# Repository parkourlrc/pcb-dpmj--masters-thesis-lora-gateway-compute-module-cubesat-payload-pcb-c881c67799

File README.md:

# Hardware design of a LoRa Gateway and in-orbit computing payload for CubeSat.

This repository contains the hardware design files from my second Master's Thesis in Telecommunications Engineering at the Polytechnic University of Valencia, Spain, 2024. The payload consists of a CubeSat-PC/104 form factor motherboard that integrates LoRa gateway hardware and a Raspberry Pi Compute Module 5 for in-orbit computing tasks. 

This project is a continuation of my previous master's thesis: [Hardware design of a LoRa Gateway payload for CubeSat.](https://github.com/dpmj/masters-thesis-lora-gateway-cubesat-payload-pcb/)

Third-party desing elements included in this repository are subject to the copyright of their respective owners.

```bibtex
@phdthesis{dpmj-master-thesis-2025,
    author = {{Del Pino Mena}, Juan},
    title = {Development of a {CubeSat} payload for in-orbit computing and {LoRa} communications},
    school = {Universitat Politècnica de València},
    year = {2025},
    month = {9},
    address = {València, Spain},
    type = {Master's thesis},
    doi = {https://doi.org/10.5281/zenodo.16641815}
}
```

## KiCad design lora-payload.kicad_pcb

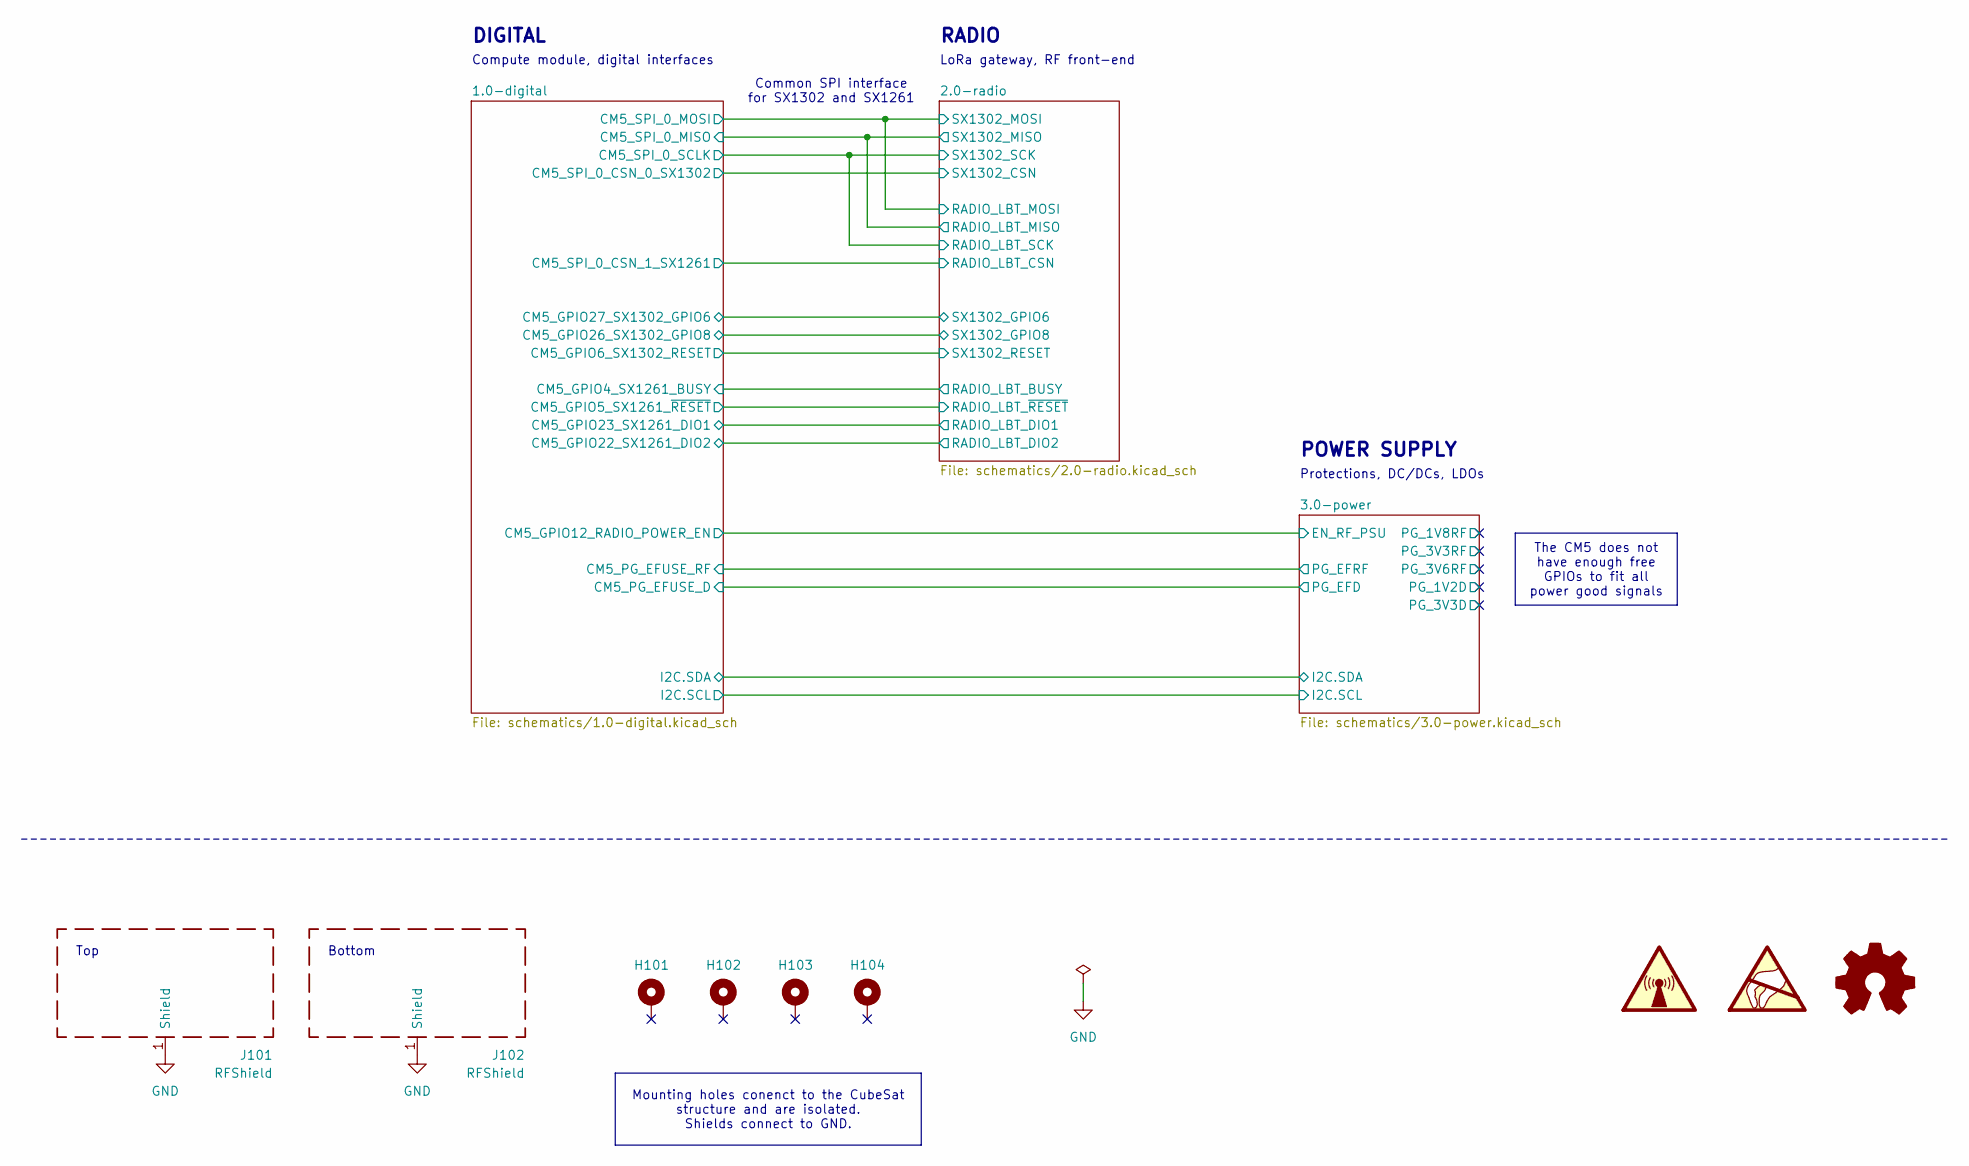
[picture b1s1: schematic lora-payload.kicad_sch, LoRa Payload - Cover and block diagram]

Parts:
H101, H102, H103, H104: MountingHole_Pad; MountingHole_3.2mm_M3_Pad
J101: RFShield; top_shield_payload
J102: RFShield; bottom_shield_payload

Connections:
GND: J101.1 (Shield), J102.1 (Shield); also elsewhere on the board

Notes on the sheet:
Protections, DC/DCs, LDOs
POWER SUPPLY
Common SPI interface for SX1302 and SX1261
Compute module, digital interfaces
LoRa gateway, RF front-end
RADIO
Top
DIGITAL
Bottom
The CM5 does not have enough free GPIOs to fit all power good signals
Mounting holes conenct to the CubeSat structure and are isolated. Shields connect to GND.

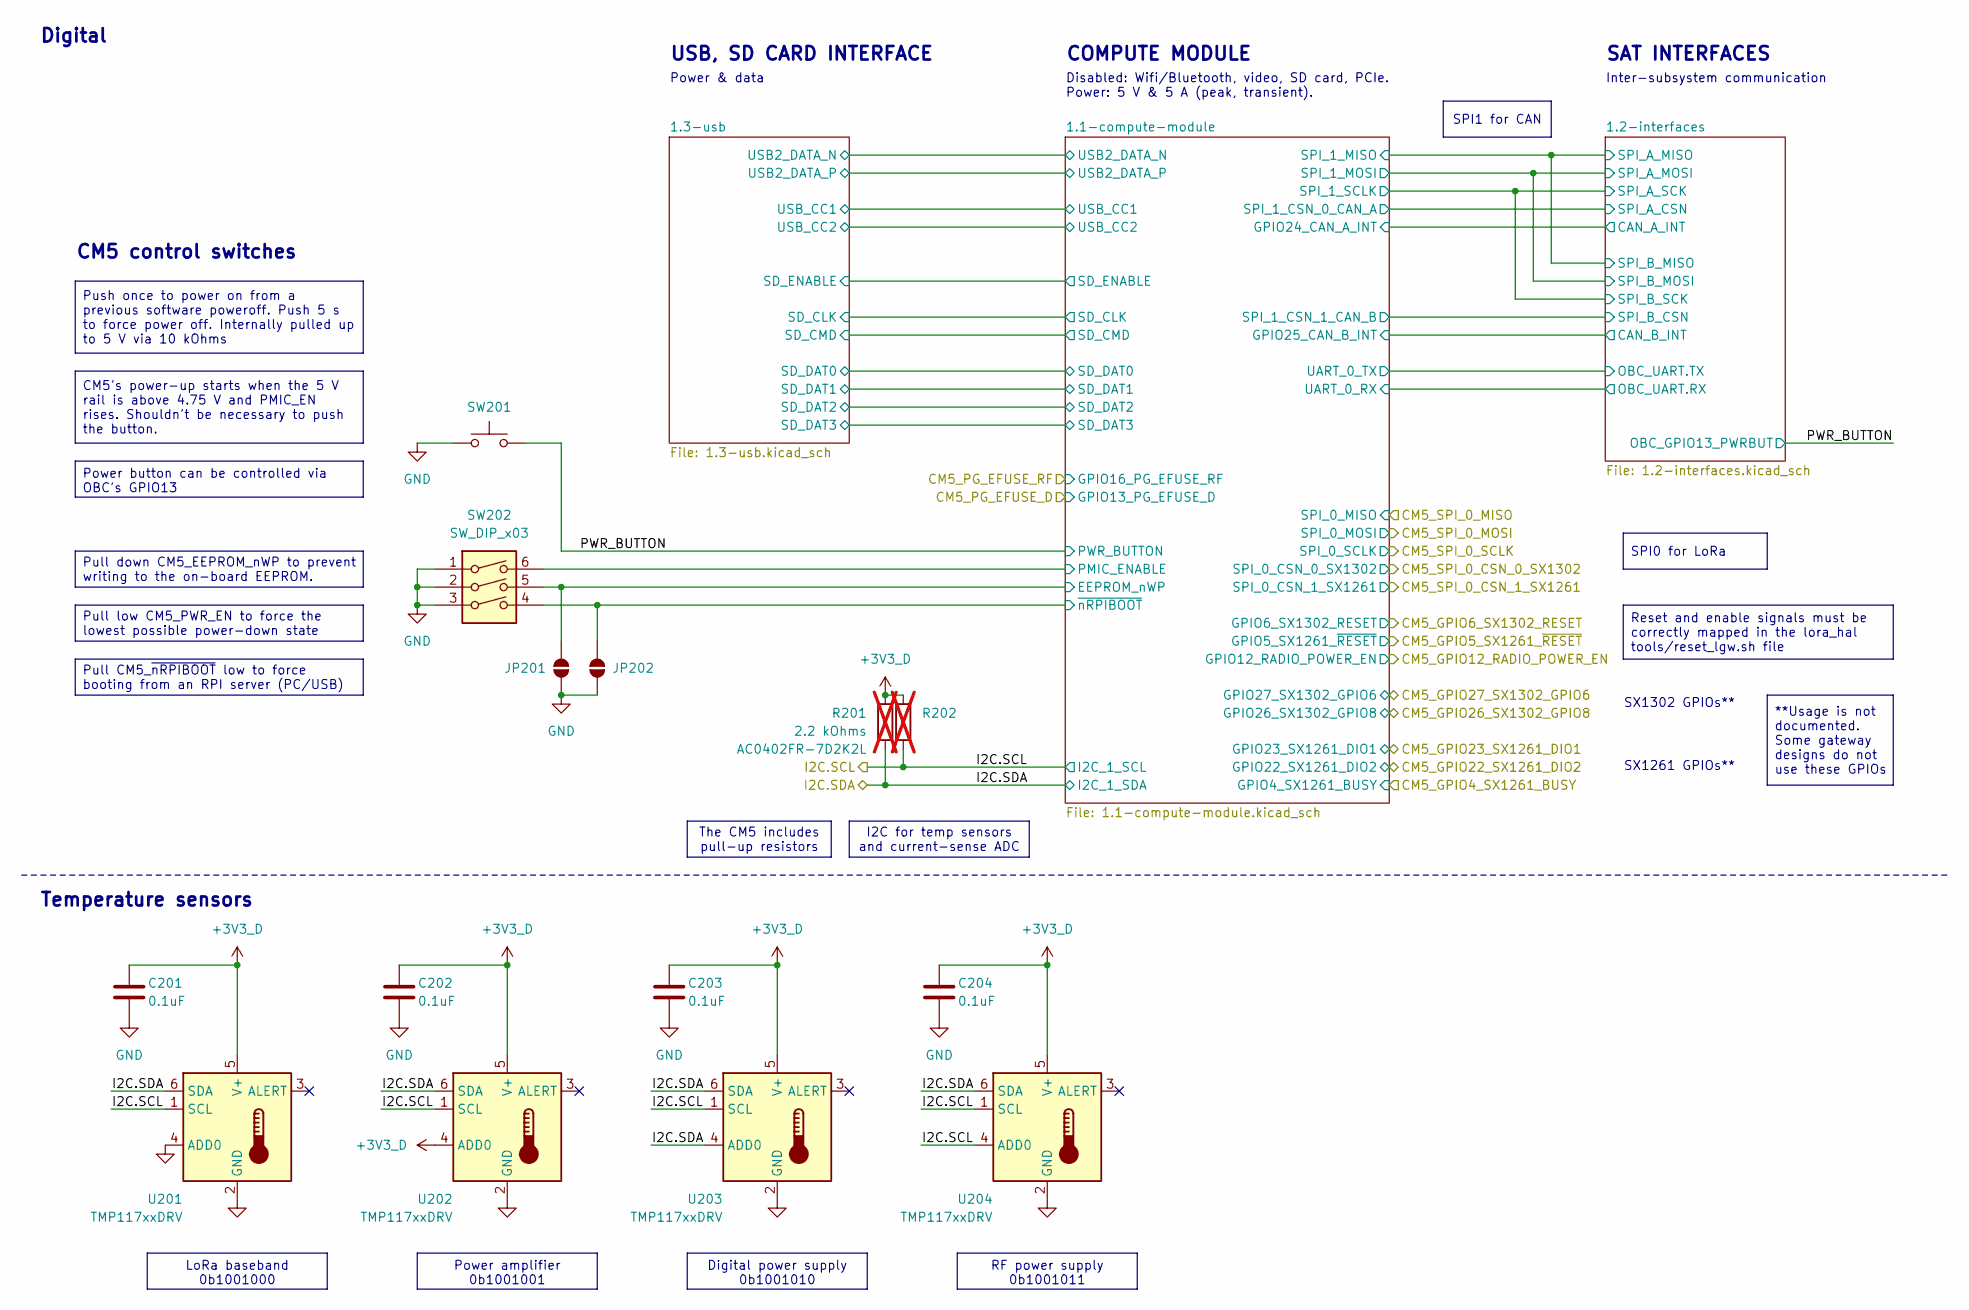
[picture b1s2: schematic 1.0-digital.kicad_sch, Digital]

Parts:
C201, C202, C203, C204: 0.1uF; C_0402_1005Metric; PartNumber GRM155R71C104KA88J
JP201, JP202: SolderJumper_2_Open; SolderJumper-2_P1.3mm_Open_RoundedPad1.0x1.5mm
R201: 2.2 kOhms; R_0402_1005Metric; PartNumber AC0402FR-7D2K2L; not fitted
R202: 2.2 kOhm; R_0402_1005Metric; PartNumber AC0402FR-7D2K2L; not fitted
SW201: SW_Push; SW_Push_1P1T_NO_Vertical_Wuerth_434133025816
SW202: SW_DIP_x03; SW_DIP_SPSTx03_Slide_KingTek_DSHP03TJ_W5.25mm_P1.27mm_JPin
U201, U202, U203, U204: TMP117xxDRV; WSON-6-1EP_2x2mm_P0.65mm_EP1x1.6mm

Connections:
+3V3_D: C201.2, C202.2, C203.2, C204.2, R201.1, R202.1, U201.5 (V+), U202.4 (ADD0), U202.5 (V+), U203.5 (V+), U204.5 (V+); also elsewhere on the board
/1.0-digital/1.1-compute-module/EEPROM_nWP: JP201.2 (B), SW202.5; also elsewhere on the board
/1.0-digital/1.1-compute-module/PMIC_ENABLE: SW202.6; also elsewhere on the board
/1.0-digital/1.1-compute-module/~nRPIBOOT: JP202.2 (B), SW202.4; also elsewhere on the board
/1.0-digital/I2C.SCL: R202.2, U201.1 (SCL), U202.1 (SCL), U203.1 (SCL), U204.1 (SCL), U204.4 (ADD0); also elsewhere on the board
/1.0-digital/I2C.SDA: R201.2, U201.6 (SDA), U202.6 (SDA), U203.4 (ADD0), U203.6 (SDA), U204.6 (SDA); also elsewhere on the board
/1.0-digital/PWR_BUTTON: SW201.2; also elsewhere on the board
GND: C201.1, C202.1, C203.1, C204.1, JP201.1 (A), JP202.1 (A), SW201.1, SW202.1, SW202.2, SW202.3, U201.2 (GND), U201.4 (ADD0), U202.2 (GND), U203.2 (GND), U204.2 (GND); also elsewhere on the board

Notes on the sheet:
SX1261 GPIOs**
SAT INTERFACES
COMPUTE MODULE
Inter-subsystem communication
Disabled: Wifi/Bluetooth, video, SD card, PCIe. Power: 5 V & 5 A (peak, transient).
Temperature sensors
Digital
USB, SD CARD INTERFACE
SX1302 GPIOs**
Power & data
CM5 control switches
SPI0 for LoRa
The CM5 includes pull-up resistors
Pull CM5_~{nRPIBOOT} low to force booting from an RPI server (PC/USB)
Pull low CM5_PWR_EN to force the lowest possible power-down state
LoRa baseband 0b1001000
SPI1 for CAN
**Usage is not documented. Some gateway designs do not use these GPIOs
CM5's power-up starts when the 5 V rail is above 4.75 V and PMIC_EN rises. Shouldn't be necessary to push the button.
RF power supply 0b1001011
Digital power supply 0b1001010
Power button can be controlled via OBC's GPIO13
Push once to power on from a previous software poweroff. Push 5 s to force power off. Internally pulled up to 5 V via 10 kOhms
Power amplifier 0b1001001
Reset and enable signals must be correctly mapped in the lora_hal tools/reset_lgw.sh file
I2C for temp sensors and current-sense ADC
Pull down CM5_EEPROM_nWP to prevent writing to the on-board EEPROM.

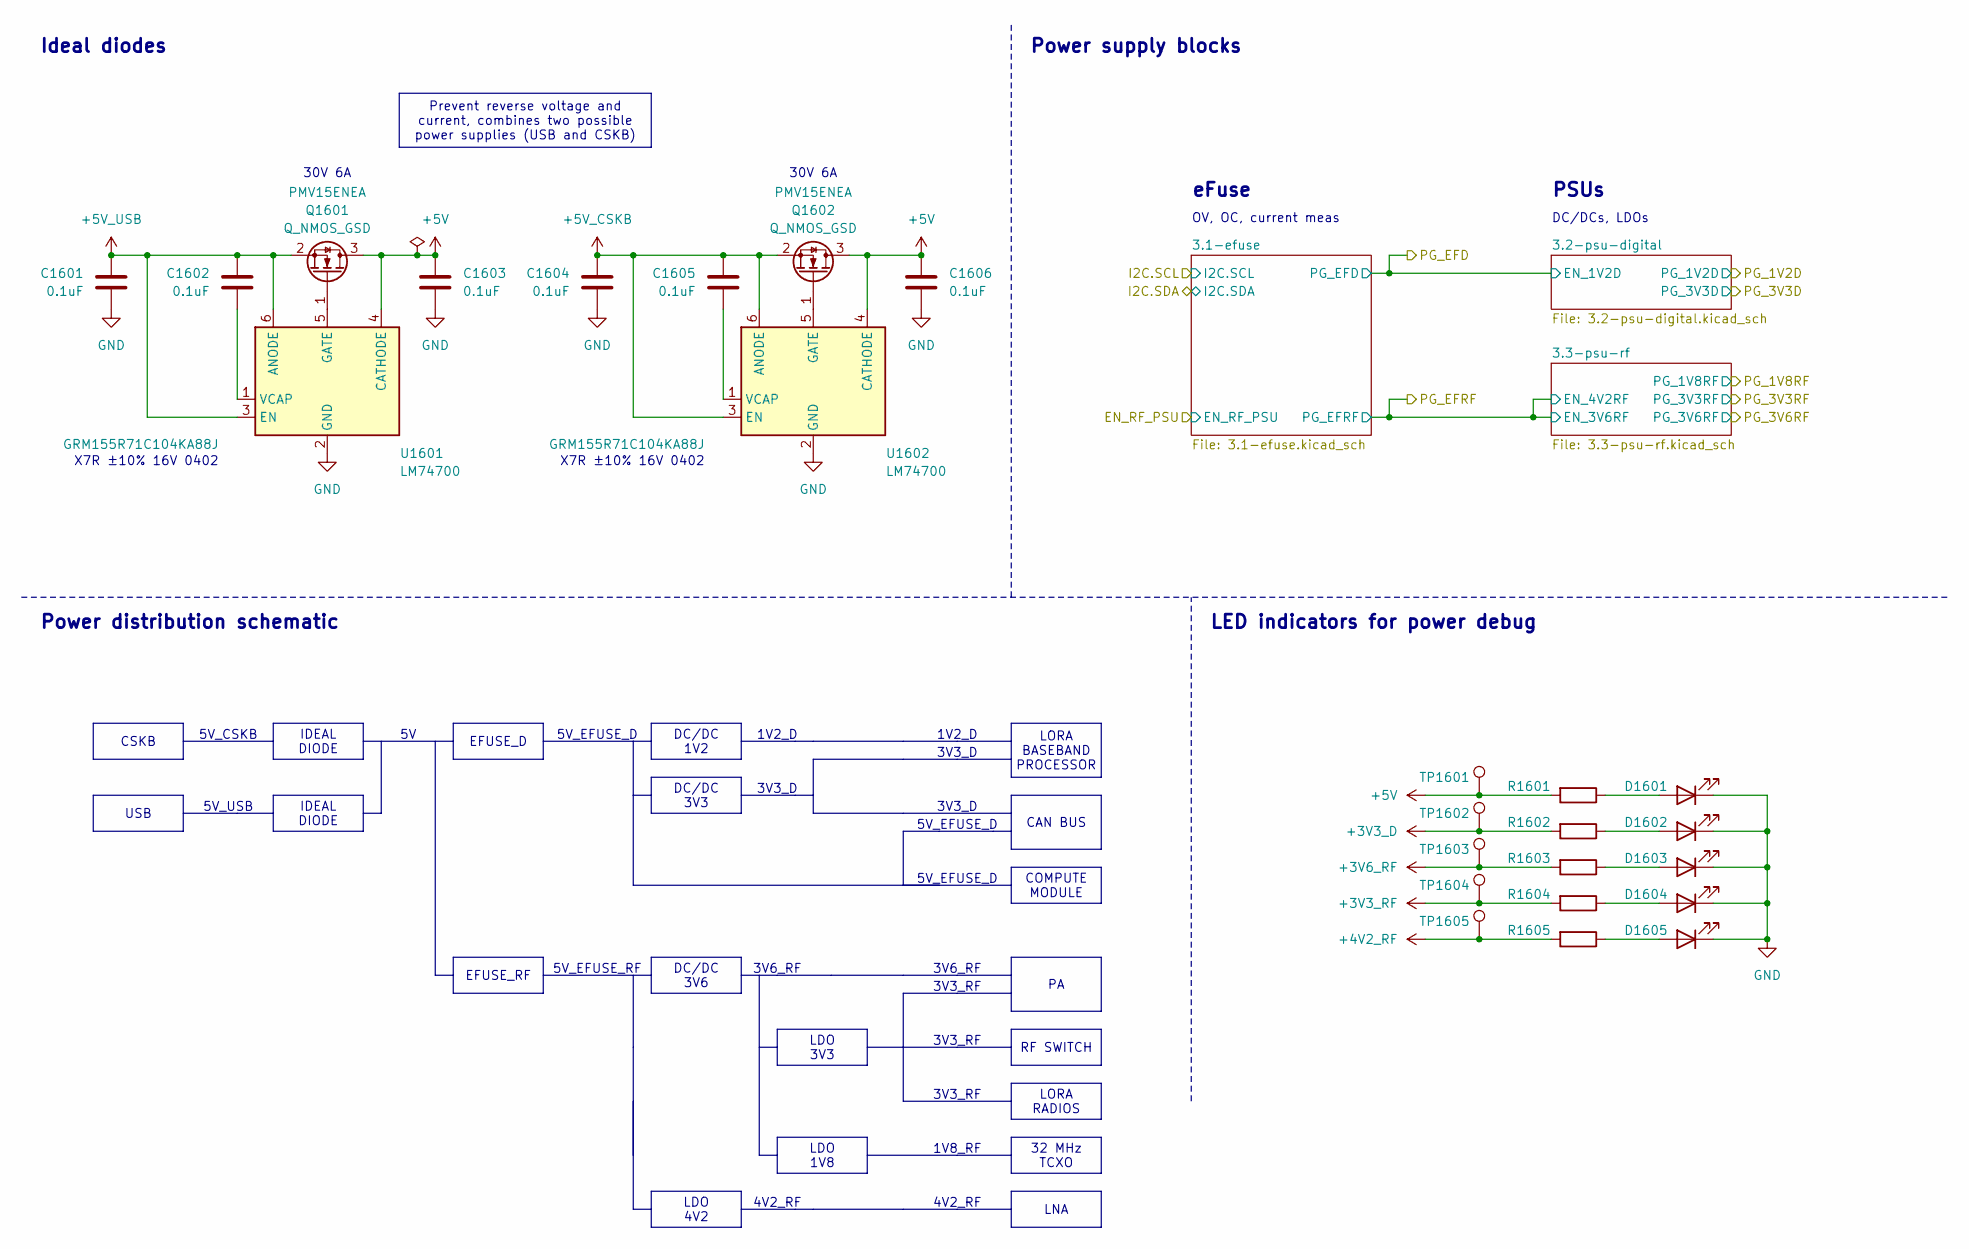
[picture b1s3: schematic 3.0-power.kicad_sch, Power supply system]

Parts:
C1601, C1602, C1603, C1604, C1605, C1606: 0.1uF; C_0402_1005Metric; PartNumber GRM155R71C104KA88J
D1601, D1602, D1603, D1604, D1605: Green; LED_0402_1005Metric
Q1601, Q1602: Q_NMOS_GSD; TSOT-23; PartNumber PMV15ENEA
R1601, R1602, R1603, R1604, R1605: 680 Ohms; R_0402_1005Metric
TP1601, TP1602, TP1603, TP1604, TP1605: TestPoint; TestPoint_Pad_D1.0mm
U1601, U1602: LM74700; SOT-23-6

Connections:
+3V3_D: R1602.2, TP1602.1; also elsewhere on the board
+3V3_RF: R1604.2, TP1604.1; also elsewhere on the board
+3V6_RF: R1603.2, TP1603.1; also elsewhere on the board
+4V2_RF: R1605.2, TP1605.1; also elsewhere on the board
+5V: C1603.2, C1606.2, Q1601.3 (D), Q1602.3 (D), R1601.2, TP1601.1, U1601.4 (CATHODE), U1602.4 (CATHODE); also elsewhere on the board
+5V_CSKB: C1604.2, C1605.2, Q1602.2 (S), U1602.3 (EN), U1602.6 (ANODE); also elsewhere on the board
+5V_USB: C1601.2, C1602.2, Q1601.2 (S), U1601.3 (EN), U1601.6 (ANODE); also elsewhere on the board
GND: C1601.1, C1603.1, C1604.1, C1606.1, D1601.1 (K), D1602.1 (K), D1603.1 (K), D1604.1 (K), D1605.1 (K), U1601.2 (GND), U1602.2 (GND); also elsewhere on the board
unnamed: D1601.2 (A), R1601.1
unnamed: D1602.2 (A), R1602.1
unnamed: D1603.2 (A), R1603.1
unnamed: D1604.2 (A), R1604.1
unnamed: D1605.2 (A), R1605.1
unnamed: Q1601.1 (G), U1601.5 (GATE)
unnamed: Q1602.1 (G), U1602.5 (GATE)
unnamed: C1602.1, U1601.1 (VCAP)
unnamed: C1605.1, U1602.1 (VCAP)

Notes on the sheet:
5V_USB
1V2_D
5V_EFUSE_D
4V2_RF
Ideal diodes
5V_CSKB
3V3_D
30V 6A
LED indicators for power debug
1V8_RF
3V3_RF
X7R ±10% 16V 0402
3V6_RF
DC/DCs, LDOs
5V_EFUSE_RF
Power distribution schematic
OV, OC, current meas
Power supply blocks
eFuse
PSUs
DC/DC 3V3
DC/DC 3V6
DC/DC 1V2
USB
EFUSE_RF
LDO 1V8
Prevent reverse voltage and current, combines two possible power supplies (USB and CSKB)
CAN BUS
RF SWITCH
IDEAL DIODE
LORA BASEBAND PROCESSOR
32 MHz TCXO
LDO 3V3
LORA RADIOS
EFUSE_D
COMPUTE MODULE
LDO 4V2
LNA
CSKB

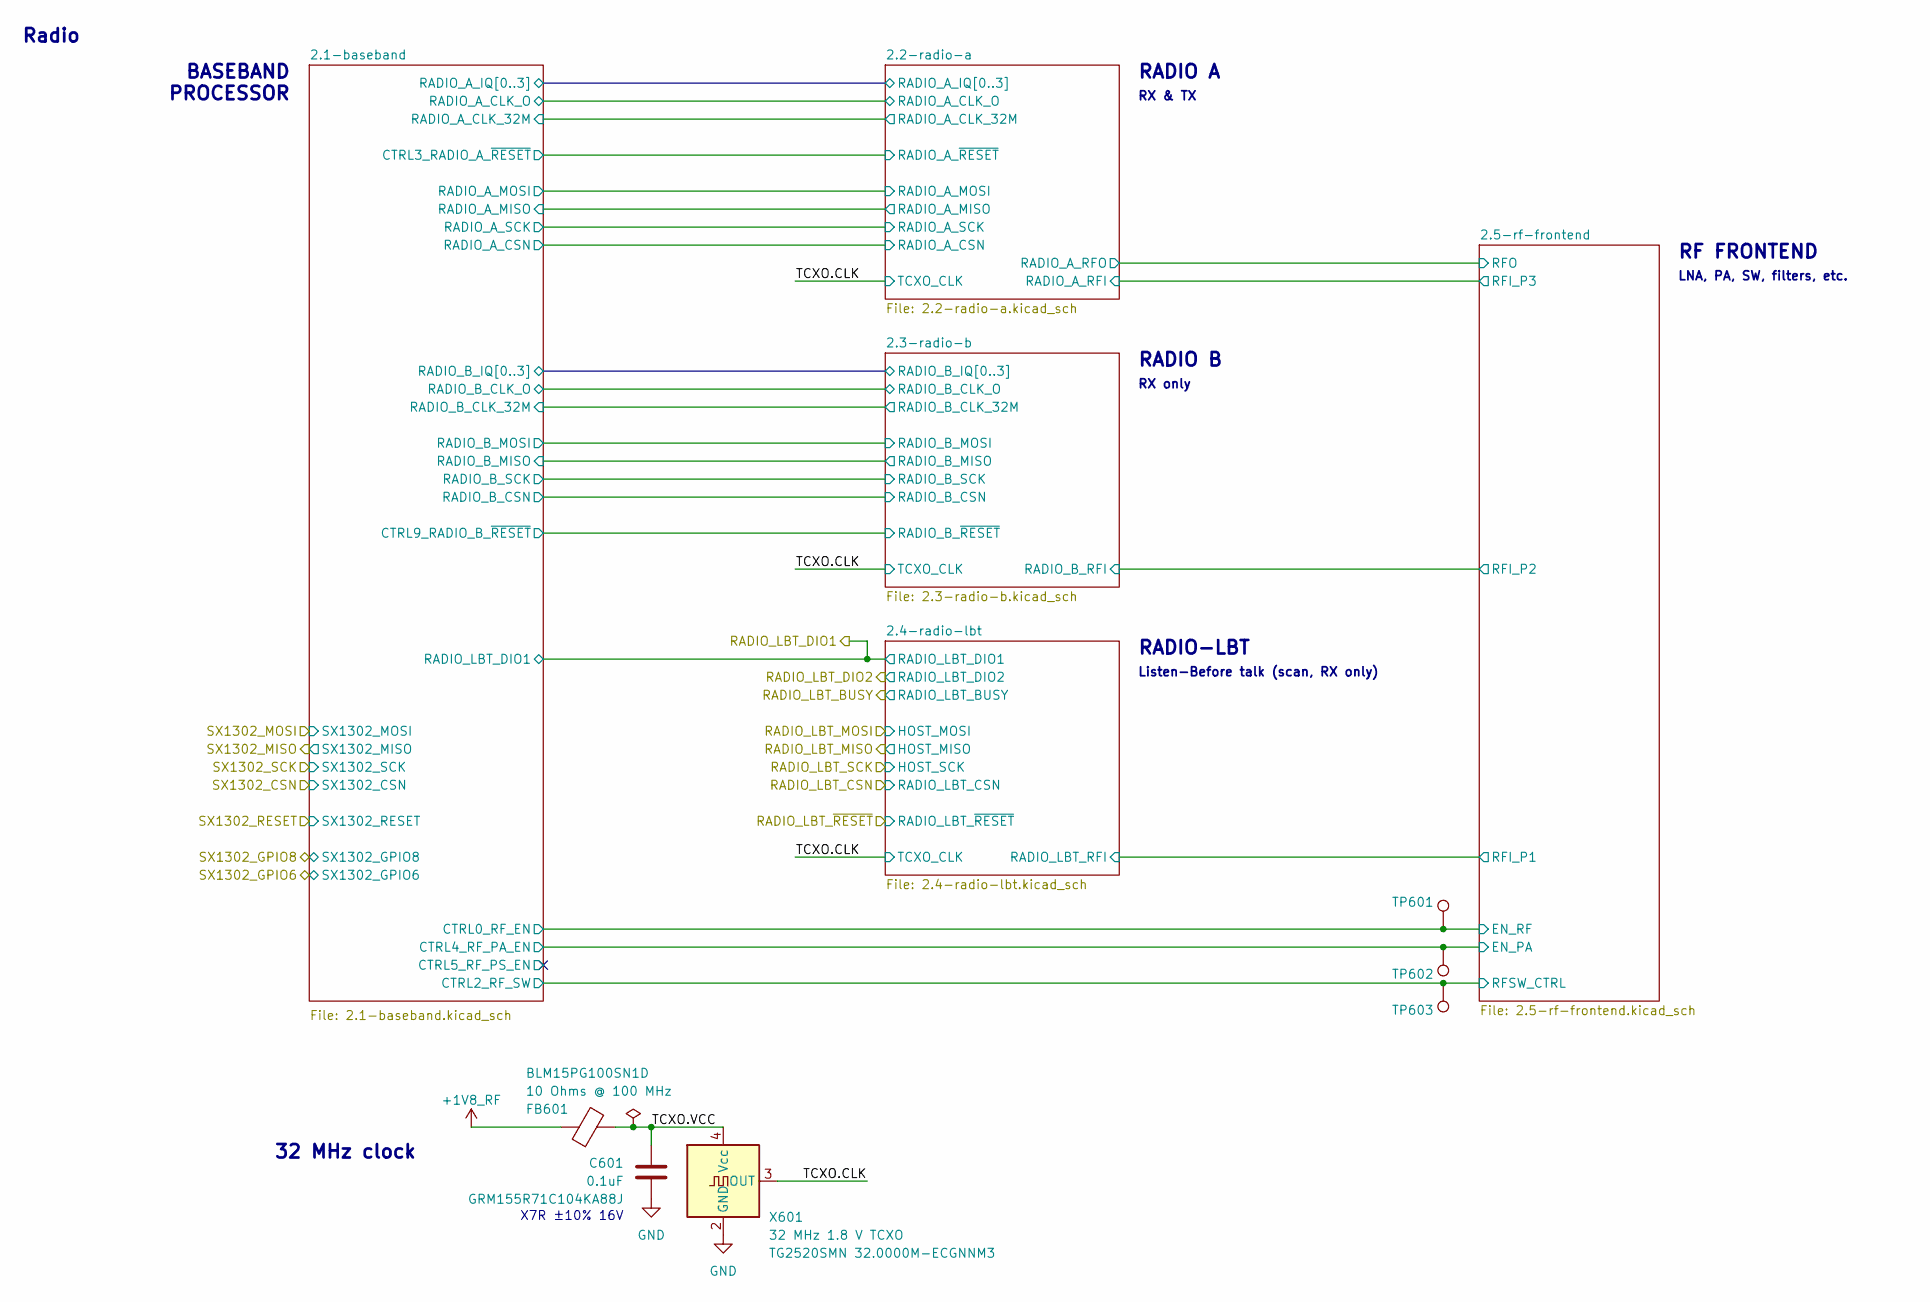
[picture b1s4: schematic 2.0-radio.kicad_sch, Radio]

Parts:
C601: 0.1uF; C_0402_1005Metric; PartNumber GRM155R71C104KA88J
FB601: 10 Ohms @ 100 MHz; L_0402_1005Metric; PartNumber BLM15PG100SN1D
TP601, TP602, TP603: TestPoint; TestPoint_Pad_D1.0mm
X601: 32 MHz 1.8 V TCXO; Oscillator_SMD_SeikoEpson_TG2520SMN-xxx-xxxxxx-4Pin_2.5x2.0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; PartNumber TG2520SMN 32.0000M-ECGNNM3

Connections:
+1V8_RF: FB601.1; also elsewhere on the board
/2.0-radio/2.1-baseband/CTRL0_RF_EN: TP601.1; also elsewhere on the board
/2.0-radio/2.1-baseband/CTRL2_RF_SW: TP603.1; also elsewhere on the board
/2.0-radio/2.1-baseband/CTRL4_RF_PA_EN: TP602.1; also elsewhere on the board
/2.0-radio/TCXO.CLK: X601.3 (OUT); also elsewhere on the board
/2.0-radio/TCXO.VCC: C601.2, FB601.2, X601.4 (Vcc)
GND: C601.1, X601.2 (GND); also elsewhere on the board

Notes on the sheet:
RADIO B
32 MHz clock
RF FRONTEND
RX & TX
LNA, PA, SW, filters, etc.
Listen-Before talk (scan, RX only)
X7R ±10% 16V
RADIO-LBT
BASEBAND PROCESSOR
RADIO A
RX only
Radio

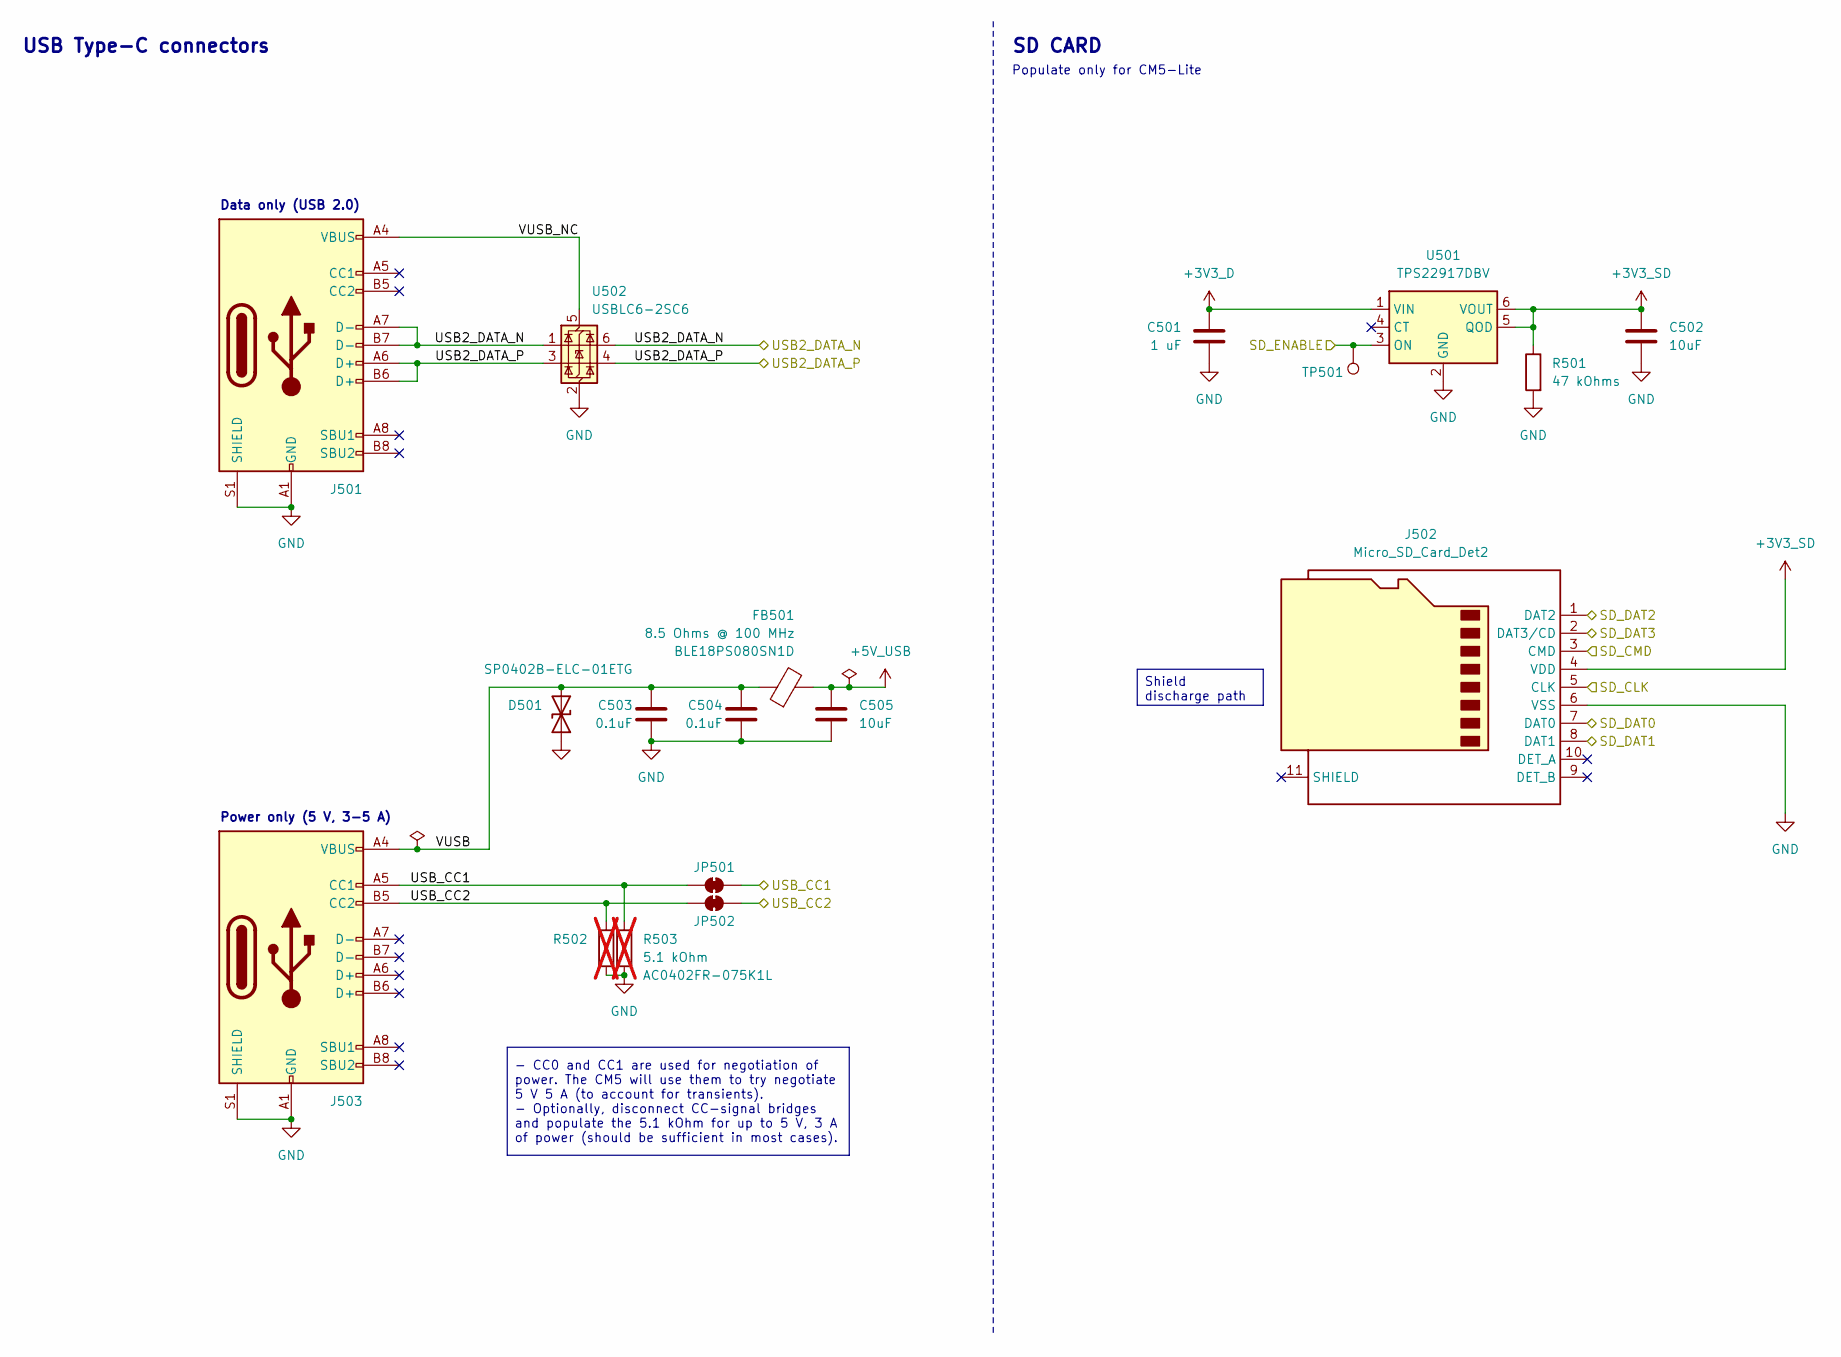
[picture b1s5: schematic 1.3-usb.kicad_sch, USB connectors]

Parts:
C501: 1 uF; C_0402_1005Metric; PartNumber GRM155Z71A105KE01J
C502, C505: 10uF; C_0603_1608Metric; PartNumber GRT21BC71E106KE13L
C503, C504: 0.1uF; C_0402_1005Metric; PartNumber GRM155R71C104KA88J
D501: SP0402B-ELC-01ETG; D_SOD-882; PartNumber SP0402B-ELC-01ETG
FB501: 8.5 Ohms @ 100 MHz; L_0603_1608Metric; PartNumber BLE18PS080SN1D
J501, J503: USB_C_Receptacle_USB2.0_16P; USB_C_Receptacle_GCT_USB4105-xx-A_16P_TopMnt_Horizontal
J502: Micro_SD_Card_Det2; microSD_HC_Hirose_DM3AT-SF-PEJM5
JP501, JP502: SolderJumper_2_Bridged; SolderJumper-2_P1.3mm_Bridged_RoundedPad1.0x1.5mm
R501: 47 kOhms; R_0402_1005Metric; PartNumber RC0402FR-0747KL
R502: 5.1 kOhm; R_0402_1005Metric; PartNumber AC0402FR-075K1L; not fitted
R503: 124 Ohms; R_0402_1005Metric; PartNumber AC0402FR-075K1L; not fitted
TP501: TestPoint; TestPoint_Pad_D1.0mm
U501: TPS22917DBV; SOT-23-6
U502: USBLC6-2SC6; SOT-23-6

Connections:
+3V3_D: C501.2, U501.1 (VIN); also elsewhere on the board
+3V3_SD: C502.2, J502.4 (VDD), R501.1, U501.5 (QOD), U501.6 (VOUT)
+5V_USB: C505.2, FB501.2; also elsewhere on the board
/1.0-digital/1.1-compute-module/SD_CLK: J502.5 (CLK); also elsewhere on the board
/1.0-digital/1.1-compute-module/SD_CMD: J502.3 (CMD); also elsewhere on the board
/1.0-digital/1.1-compute-module/SD_DAT0: J502.7 (DAT0); also elsewhere on the board
/1.0-digital/1.1-compute-module/SD_DAT1: J502.8 (DAT1); also elsewhere on the board
/1.0-digital/1.1-compute-module/SD_DAT2: J502.1 (DAT2); also elsewhere on the board
/1.0-digital/1.1-compute-module/SD_DAT3: J502.2 (DAT3/CD); also elsewhere on the board
/1.0-digital/1.1-compute-module/SD_ENABLE: TP501.1, U501.3 (ON); also elsewhere on the board
/1.0-digital/1.3-usb/USB2_DATA_N: J501.A7 (D-), J501.B7 (D-), U502.1 (I/O1), U502.6 (I/O1); also elsewhere on the board
/1.0-digital/1.3-usb/USB2_DATA_P: J501.A6 (D+), J501.B6 (D+), U502.3 (I/O2), U502.4 (I/O2); also elsewhere on the board
/1.0-digital/1.3-usb/USB_CC1: J503.A5 (CC1), JP501.1 (A), JP501.2 (B), R503.2; also elsewhere on the board
/1.0-digital/1.3-usb/USB_CC2: J503.B5 (CC2), JP502.1 (A), JP502.2 (B), R502.2; also elsewhere on the board
/1.0-digital/1.3-usb/VUSB: C503.2, C504.2, D501.2 (A2), FB501.1, J503.A4 (VBUS), J503.A9 (VBUS), J503.B4 (VBUS), J503.B9 (VBUS)
/1.0-digital/1.3-usb/VUSB_NC: J501.A4 (VBUS), J501.A9 (VBUS), J501.B4 (VBUS), J501.B9 (VBUS), U502.5 (VBUS)
GND: C501.1, C502.1, C503.1, C504.1, C505.1, D501.1 (A1), J501.A1 (GND), J501.A12 (GND), J501.B1 (GND), J501.B12 (GND), J501.S1 (SHIELD), J502.6 (VSS), J503.A1 (GND), J503.A12 (GND), J503.B1 (GND), J503.B12 (GND), J503.S1 (SHIELD), R501.2, R502.1, R503.1, U501.2 (GND), U502.2 (GND); also elsewhere on the board

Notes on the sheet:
Power only (5 V, 3-5 A)
SD CARD
USB Type-C connectors
Data only (USB 2.0)
Populate only for CM5-Lite
Shield discharge path
- CC0 and CC1 are used for negotiation of power. The CM5 will use them to try negotiate 5 V 5 A (to account for transients). - Optionally, disconnect CC-signal bridges and populate the 5.1 kOhm for up to 5 V, 3 A of power (should be sufficient in most cases).
